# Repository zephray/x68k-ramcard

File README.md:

# x68k-ramcard
RAM Expansion Board for SHARP X68000

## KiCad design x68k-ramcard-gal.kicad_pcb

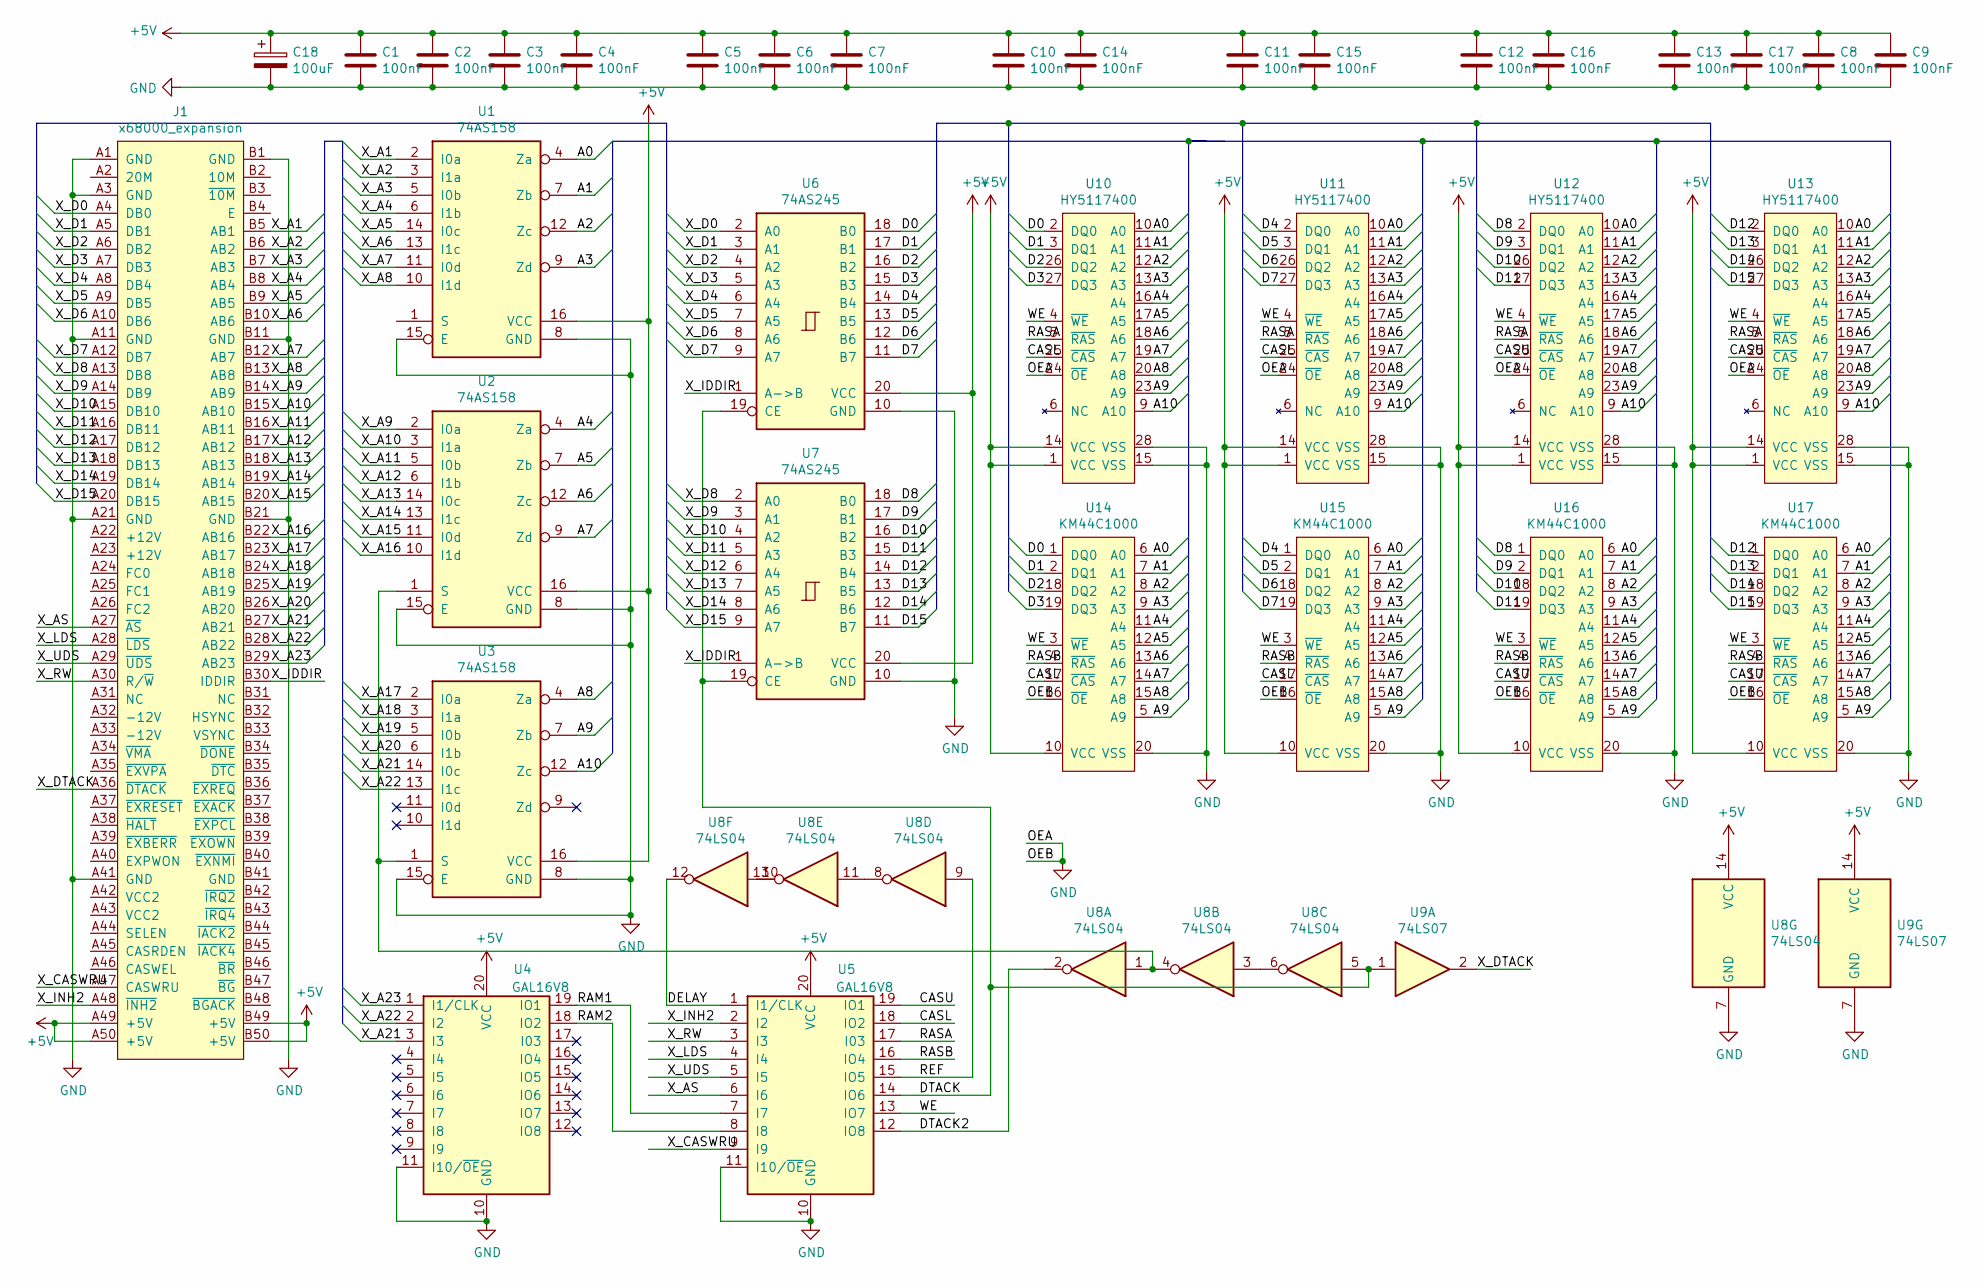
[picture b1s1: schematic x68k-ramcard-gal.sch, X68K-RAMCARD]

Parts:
C1, C2, C3, C4, C5, C6, C7, C8, C9, C10, C11, C12, C13, C14, C15, C16, C17: 100nF; CP_Radial_Tantal_D4.5mm_P2.50mm
C18: 100uF; CP_Radial_D7.5mm_P2.50mm
J1: x68000_expansion
U1, U2, U3: 74AS158; DIP-16_W7.62mm_Socket
U4, U5: GAL16V8; DIP-20_W7.62mm_Socket
U6, U7: 74AS245; DIP-20_W7.62mm_Socket
U8: 74LS04; DIP-14_W7.62mm_Socket
U9: 74LS07; DIP-14_W7.62mm_Socket
U10, U11, U12, U13: HY5117400; SOJ-24
U14, U15, U16, U17: KM44C1000; SOJ-20

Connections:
+5V: C1.1, C2.1, C3.1, C4.1, C5.1, C6.1, C7.1, C8.1, C9.1, C10.1, C11.1, C12.1, C13.1, C14.1, C15.1, C16.1, C17.1, C18.1, J1.A49 (+5V), J1.A50 (+5V), J1.B49 (+5V), J1.B50 (+5V), U1.16 (VCC), U2.16 (VCC), U3.16 (VCC), U4.20 (VCC), U5.20 (VCC), U6.20 (VCC), U7.20 (VCC), U8.14 (VCC), U9.14 (VCC), U10.1 (VCC), U10.14 (VCC), U11.1 (VCC), U11.14 (VCC), U12.1 (VCC), U12.14 (VCC), U13.1 (VCC), U13.14 (VCC), U14.10 (VCC), U15.10 (VCC), U16.10 (VCC), U17.10 (VCC)
/A0: U1.4 (Za), U10.10 (A0), U11.10 (A0), U12.10 (A0), U13.10 (A0), U14.6 (A0), U15.6 (A0), U16.6 (A0), U17.6 (A0)
/A1: U1.7 (Zb), U10.11 (A1), U11.11 (A1), U12.11 (A1), U13.11 (A1), U14.7 (A1), U15.7 (A1), U16.7 (A1), U17.7 (A1)
/A2: U1.12 (Zc), U10.12 (A2), U11.12 (A2), U12.12 (A2), U13.12 (A2), U14.8 (A2), U15.8 (A2), U16.8 (A2), U17.8 (A2)
/A3: U1.9 (Zd), U10.13 (A3), U11.13 (A3), U12.13 (A3), U13.13 (A3), U14.9 (A3), U15.9 (A3), U16.9 (A3), U17.9 (A3)
/A4: U2.4 (Za), U10.16 (A4), U11.16 (A4), U12.16 (A4), U13.16 (A4), U14.11 (A4), U15.11 (A4), U16.11 (A4), U17.11 (A4)
/A5: U2.7 (Zb), U10.17 (A5), U11.17 (A5), U12.17 (A5), U13.17 (A5), U14.12 (A5), U15.12 (A5), U16.12 (A5), U17.12 (A5)
/A6: U2.12 (Zc), U10.18 (A6), U11.18 (A6), U12.18 (A6), U13.18 (A6), U14.13 (A6), U15.13 (A6), U16.13 (A6), U17.13 (A6)
/A7: U2.9 (Zd), U10.19 (A7), U11.19 (A7), U12.19 (A7), U13.19 (A7), U14.14 (A7), U15.14 (A7), U16.14 (A7), U17.14 (A7)
/A8: U3.4 (Za), U10.20 (A8), U11.20 (A8), U12.20 (A8), U13.20 (A8), U14.15 (A8), U15.15 (A8), U16.15 (A8), U17.15 (A8)
/A9: U3.7 (Zb), U10.23 (A9), U11.23 (A9), U12.23 (A9), U13.23 (A9), U14.5 (A9), U15.5 (A9), U16.5 (A9), U17.5 (A9)
/A10: U3.12 (Zc), U10.9 (A10), U11.9 (A10), U12.9 (A10), U13.9 (A10)
/CASL: U5.18 (IO2), U10.25 (~CAS), U11.25 (~CAS), U14.17 (~CAS), U15.17 (~CAS)
/CASU: U5.19 (IO1), U12.25 (~CAS), U13.25 (~CAS), U16.17 (~CAS), U17.17 (~CAS)
/D0: U6.18 (B0), U10.2 (DQ0), U14.1 (DQ0)
/D1: U6.17 (B1), U10.3 (DQ1), U14.2 (DQ1)
/D2: U6.16 (B2), U10.26 (DQ2), U14.18 (DQ2)
/D3: U6.15 (B3), U10.27 (DQ3), U14.19 (DQ3)
/D4: U6.14 (B4), U11.2 (DQ0), U15.1 (DQ0)
/D5: U6.13 (B5), U11.3 (DQ1), U15.2 (DQ1)
/D6: U6.12 (B6), U11.26 (DQ2), U15.18 (DQ2)
/D7: U6.11 (B7), U11.27 (DQ3), U15.19 (DQ3)
/D8: U7.18 (B0), U12.2 (DQ0), U16.1 (DQ0)
/D9: U7.17 (B1), U12.3 (DQ1), U16.2 (DQ1)
/D10: U7.16 (B2), U12.26 (DQ2), U16.18 (DQ2)
/D11: U7.15 (B3), U12.27 (DQ3), U16.19 (DQ3)
/D12: U7.14 (B4), U13.2 (DQ0), U17.1 (DQ0)
/D13: U7.13 (B5), U13.3 (DQ1), U17.2 (DQ1)
/D14: U7.12 (B6), U13.26 (DQ2), U17.18 (DQ2)
/D15: U7.11 (B7), U13.27 (DQ3), U17.19 (DQ3)
/DELAY: U5.1 (I1/CLK), U8.12
/DTACK: U5.14 (IO6), U6.19 (CE), U7.19 (CE), U8.5, U9.1
/DTACK2: U5.12 (IO8), U8.2
/RAM1: U4.19 (IO1), U5.7 (I7)
/RAM2: U4.18 (IO2), U5.8 (I8)
/RASA: U5.17 (I03), U10.5 (~RAS), U11.5 (~RAS), U12.5 (~RAS), U13.5 (~RAS)
/RASB: U5.16 (IO4), U14.4 (~RAS), U15.4 (~RAS), U16.4 (~RAS), U17.4 (~RAS)
/REF: U5.15 (IO5), U8.9
/WE: U5.13 (IO7), U10.4 (~WE), U11.4 (~WE), U12.4 (~WE), U13.4 (~WE), U14.3 (~WE), U15.3 (~WE), U16.3 (~WE), U17.3 (~WE)
/X_A1: J1.B5 (AB1), U1.2 (I0a)
/X_A2: J1.B6 (AB2), U1.3 (I1a)
/X_A3: J1.B7 (AB3), U1.5 (I0b)
/X_A4: J1.B8 (AB4), U1.6 (I1b)
/X_A5: J1.B9 (AB5), U1.14 (I0c)
/X_A6: J1.B10 (AB6), U1.13 (I1c)
/X_A7: J1.B12 (AB7), U1.11 (I0d)
/X_A8: J1.B13 (AB8), U1.10 (I1d)
/X_A9: J1.B14 (AB9), U2.2 (I0a)
/X_A10: J1.B15 (AB10), U2.3 (I1a)
/X_A11: J1.B16 (AB11), U2.5 (I0b)
/X_A12: J1.B17 (AB12), U2.6 (I1b)
/X_A13: J1.B18 (AB13), U2.14 (I0c)
/X_A14: J1.B19 (AB14), U2.13 (I1c)
/X_A15: J1.B20 (AB15), U2.11 (I0d)
/X_A16: J1.B22 (AB16), U2.10 (I1d)
/X_A17: J1.B23 (AB17), U3.2 (I0a)
/X_A18: J1.B24 (AB18), U3.3 (I1a)
/X_A19: J1.B25 (AB19), U3.5 (I0b)
/X_A20: J1.B26 (AB20), U3.6 (I1b)
/X_A21: J1.B27 (AB21), U3.14 (I0c), U4.3 (I3)
/X_A22: J1.B28 (AB22), U3.13 (I1c), U4.2 (I2)
/X_A23: J1.B29 (AB23), U4.1 (I1/CLK)
/X_AS: J1.A27 (~AS), U5.6 (I6)
/X_CASWRU: J1.A47 (CASWRU), U5.9 (I9)
/X_D0: J1.A4 (DB0), U6.2 (A0)
/X_D1: J1.A5 (DB1), U6.3 (A1)
/X_D2: J1.A6 (DB2), U6.4 (A2)
/X_D3: J1.A7 (DB3), U6.5 (A3)
/X_D4: J1.A8 (DB4), U6.6 (A4)
/X_D5: J1.A9 (DB5), U6.7 (A5)
/X_D6: J1.A10 (DB6), U6.8 (A6)
/X_D7: J1.A12 (DB7), U6.9 (A7)
/X_D8: J1.A13 (DB8), U7.2 (A0)
/X_D9: J1.A14 (DB9), U7.3 (A1)
/X_D10: J1.A15 (DB10), U7.4 (A2)
/X_D11: J1.A16 (DB11), U7.5 (A3)
/X_D12: J1.A17 (DB12), U7.6 (A4)
/X_D13: J1.A18 (DB13), U7.7 (A5)
/X_D14: J1.A19 (DB14), U7.8 (A6)
/X_D15: J1.A20 (DB15), U7.9 (A7)
/X_DTACK: J1.A36 (~DTACK), U9.2
/X_IDDIR: J1.B30 (IDDIR), U6.1 (A->B), U7.1 (A->B)
/X_INH2: J1.A48 (~INH2), U5.2 (I2)
/X_LDS: J1.A28 (~LDS), U5.4 (I4)
/X_RW: J1.A30 (R/~W), U5.3 (I3)
/X_UDS: J1.A29 (~UDS), U5.5 (I5)
GND: C1.2, C2.2, C3.2, C4.2, C5.2, C6.2, C7.2, C8.2, C9.2, C10.2, C11.2, C12.2, C13.2, C14.2, C15.2, C16.2, C17.2, C18.2, J1.A1 (GND), J1.A3 (GND), J1.A11 (GND), J1.A21 (GND), J1.A41 (GND), J1.B1 (GND), J1.B11 (GND), J1.B21 (GND), U1.8 (GND), U1.15 (E), U2.8 (GND), U2.15 (E), U3.8 (GND), U3.15 (E), U4.10 (GND), U4.11 (I10/~OE~), U5.10 (GND), U5.11 (I10/~OE~), U6.10 (GND), U7.10 (GND), U8.7 (GND), U9.7 (GND), U10.15 (VSS), U10.24 (~OE), U10.28 (VSS), U11.15 (VSS), U11.24 (~OE), U11.28 (VSS), U12.15 (VSS), U12.24 (~OE), U12.28 (VSS), U13.15 (VSS), U13.24 (~OE), U13.28 (VSS), U14.16 (~OE), U14.20 (VSS), U15.16 (~OE), U15.20 (VSS), U16.16 (~OE), U16.20 (VSS), U17.16 (~OE), U17.20 (VSS)
unnamed: U2.1 (S), U3.1 (S), U8.1, U8.4
unnamed: U8.3, U8.6
unnamed: U8.8, U8.11

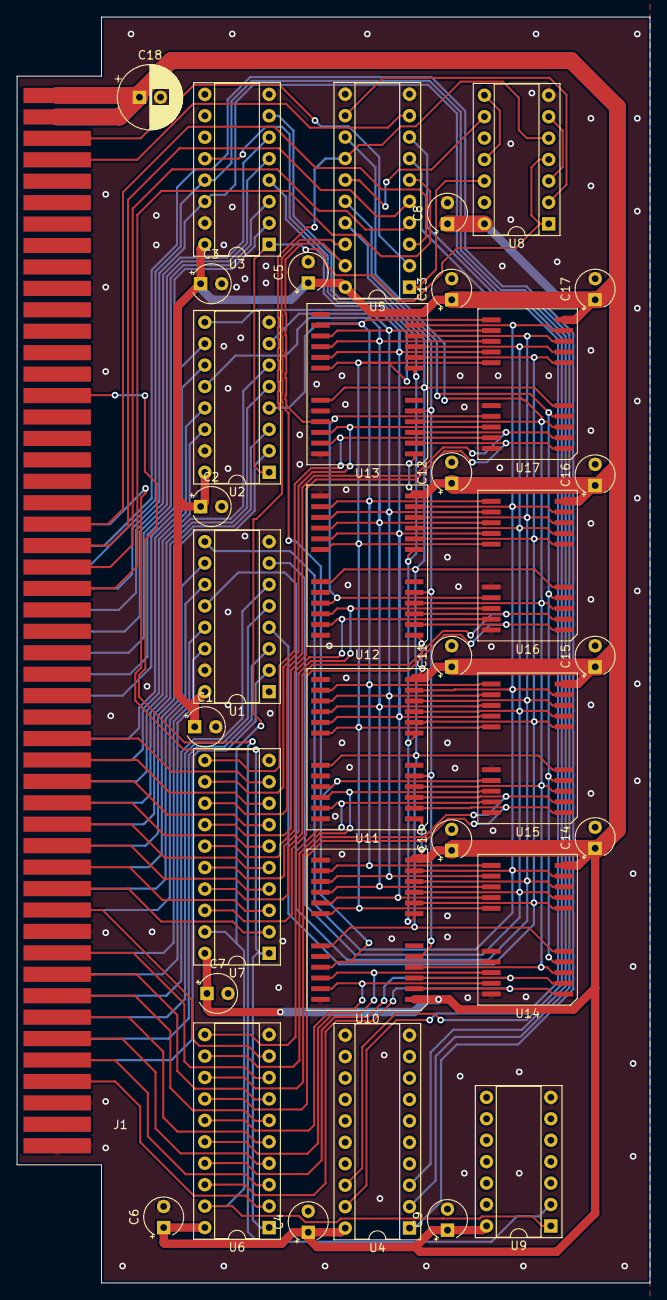
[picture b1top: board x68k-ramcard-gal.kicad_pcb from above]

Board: 2 copper layers, 75.0 x 150.0 mm, 36 parts (0 on the bottom side), 90 nets.

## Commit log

2019-08-18 schematics
2019-08-20 finish layout
2019-08-27 gal: add gal sources
